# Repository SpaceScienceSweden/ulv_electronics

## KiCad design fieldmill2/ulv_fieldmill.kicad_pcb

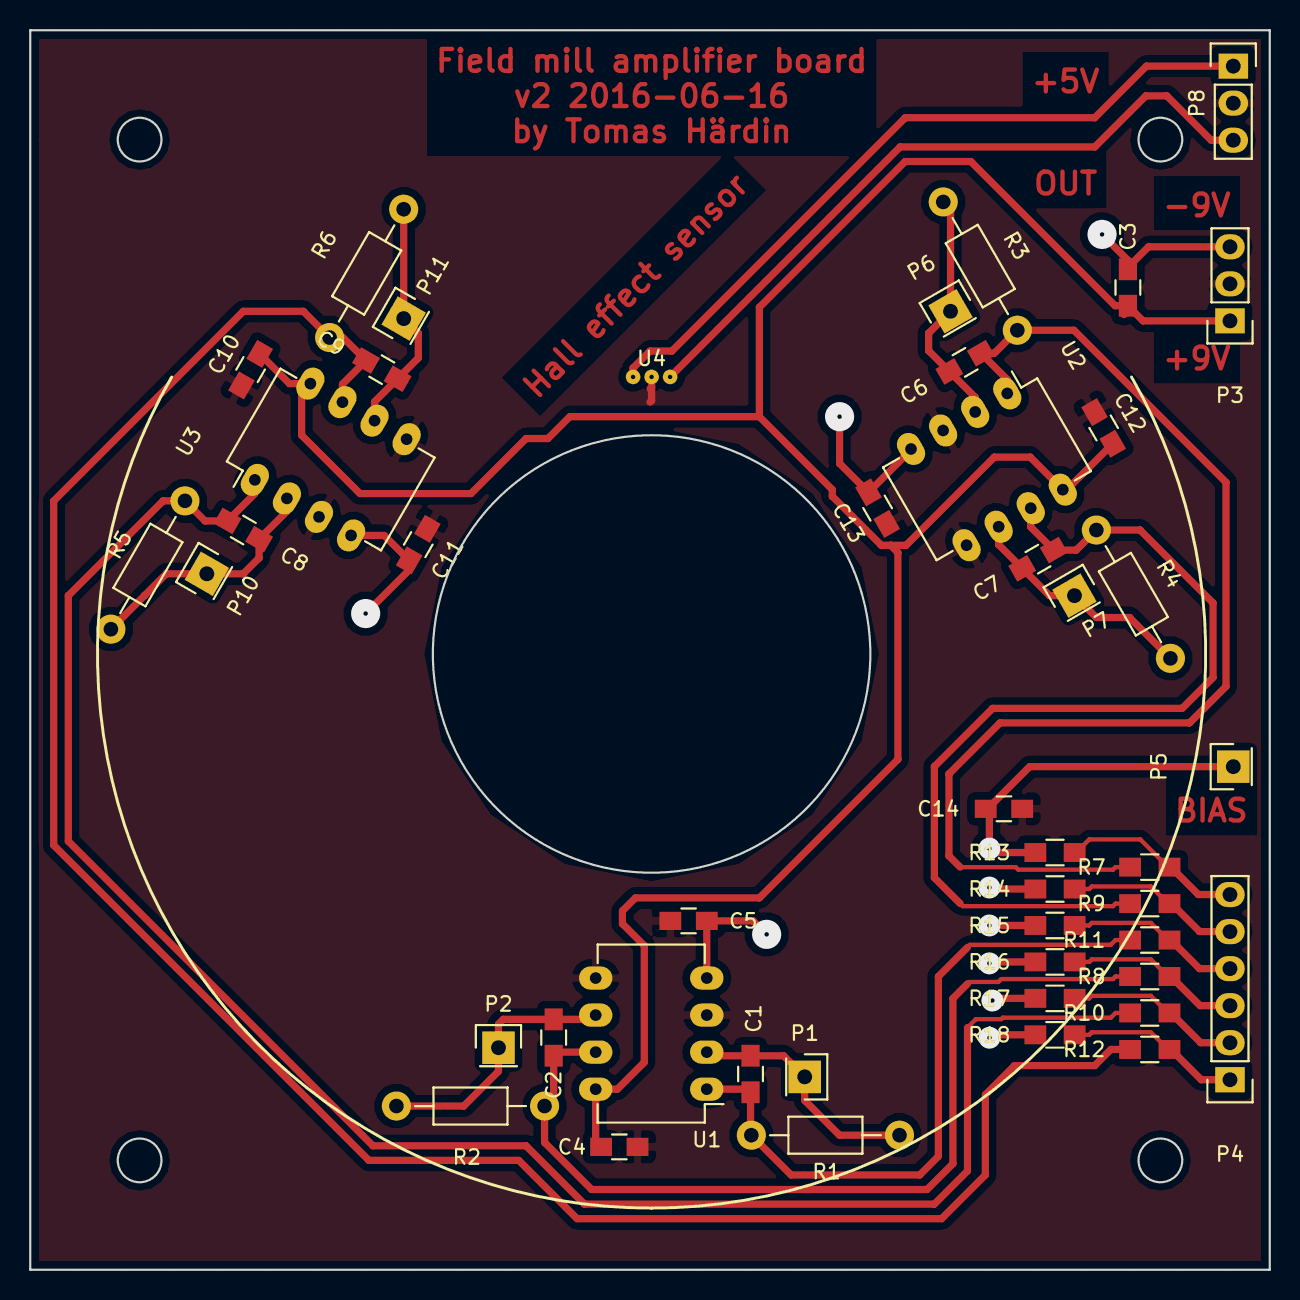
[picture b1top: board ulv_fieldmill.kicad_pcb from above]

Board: 4 copper layers, 85.0 x 85.0 mm, 46 parts (0 on the bottom side), 24 nets.

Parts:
C1, C2, C6, C7, C8, C9: 1p; C_0805_HandSoldering
C3, C14: 1u; C_0805_HandSoldering
C4, C5, C10, C11, C12, C13: 100n; C_0805_HandSoldering
P1, P2, P5, P6, P7, P10, P11: CONN_01X01; Pin_Header_Straight_1x01
P3, P8: CONN_01X03; Pin_Header_Straight_1x03
P4: CONN_01X06; Pin_Header_Straight_1x06
R1, R2, R3, R4, R5, R6: 100M; Resistor_Horizontal_RM10mm
R7, R8, R9, R10, R11, R12, R13, R14, R15, R16, R17, R18: 10k; R_0805_HandSoldering
U1, U2, U3: OPA2604; DIP-8_W7.62mm_LongPads
U4: A3506LU; 3x50mil

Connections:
+5V: P8.1, U4.1
+9VA: C3.2, C4.2, C10.2, C12.2, P3.1, U1.8, U2.8, U3.8
-9VA: C3.1, C5.1, C11.1, C13.1, P3.3, U1.4, U2.4, U3.4
GND: C4.1, C5.2, C10.1, C11.2, C12.1, C13.2, C14.1, P3.2, P8.2, U1.3, U1.5, U2.3, U2.5, U3.3, U3.5, U4.2
unnamed: C1.1, R1.1, R11.2, U1.1
unnamed: C1.2, P1.1, R1.2, U1.2
unnamed: C2.1, R2.1, R8.2, U1.7
unnamed: C2.2, P2.1, R2.2, U1.6
unnamed: C6.1, R3.1, R7.2, U2.1
unnamed: C6.2, P6.1, R3.2, U2.2
unnamed: C7.1, R4.1, R9.2, U2.7
unnamed: C7.2, P7.1, R4.2, U2.6
unnamed: C8.1, R5.1, R10.2, U3.1
unnamed: C8.2, P10.1, R5.2, U3.2
unnamed: C9.1, R6.1, R12.2, U3.7
unnamed: C9.2, P11.1, R6.2, U3.6
unnamed: C14.2, P5.1, R13.2, R14.2, R15.2, R16.2, R17.2, R18.2
unnamed: P4.1, R12.1, R18.1
unnamed: P4.2, R10.1, R17.1
unnamed: P4.3, R8.1, R16.1
unnamed: P4.4, R11.1, R15.1
unnamed: P4.5, R9.1, R14.1
unnamed: P4.6, R7.1, R13.1
unnamed: P8.3, U4.3

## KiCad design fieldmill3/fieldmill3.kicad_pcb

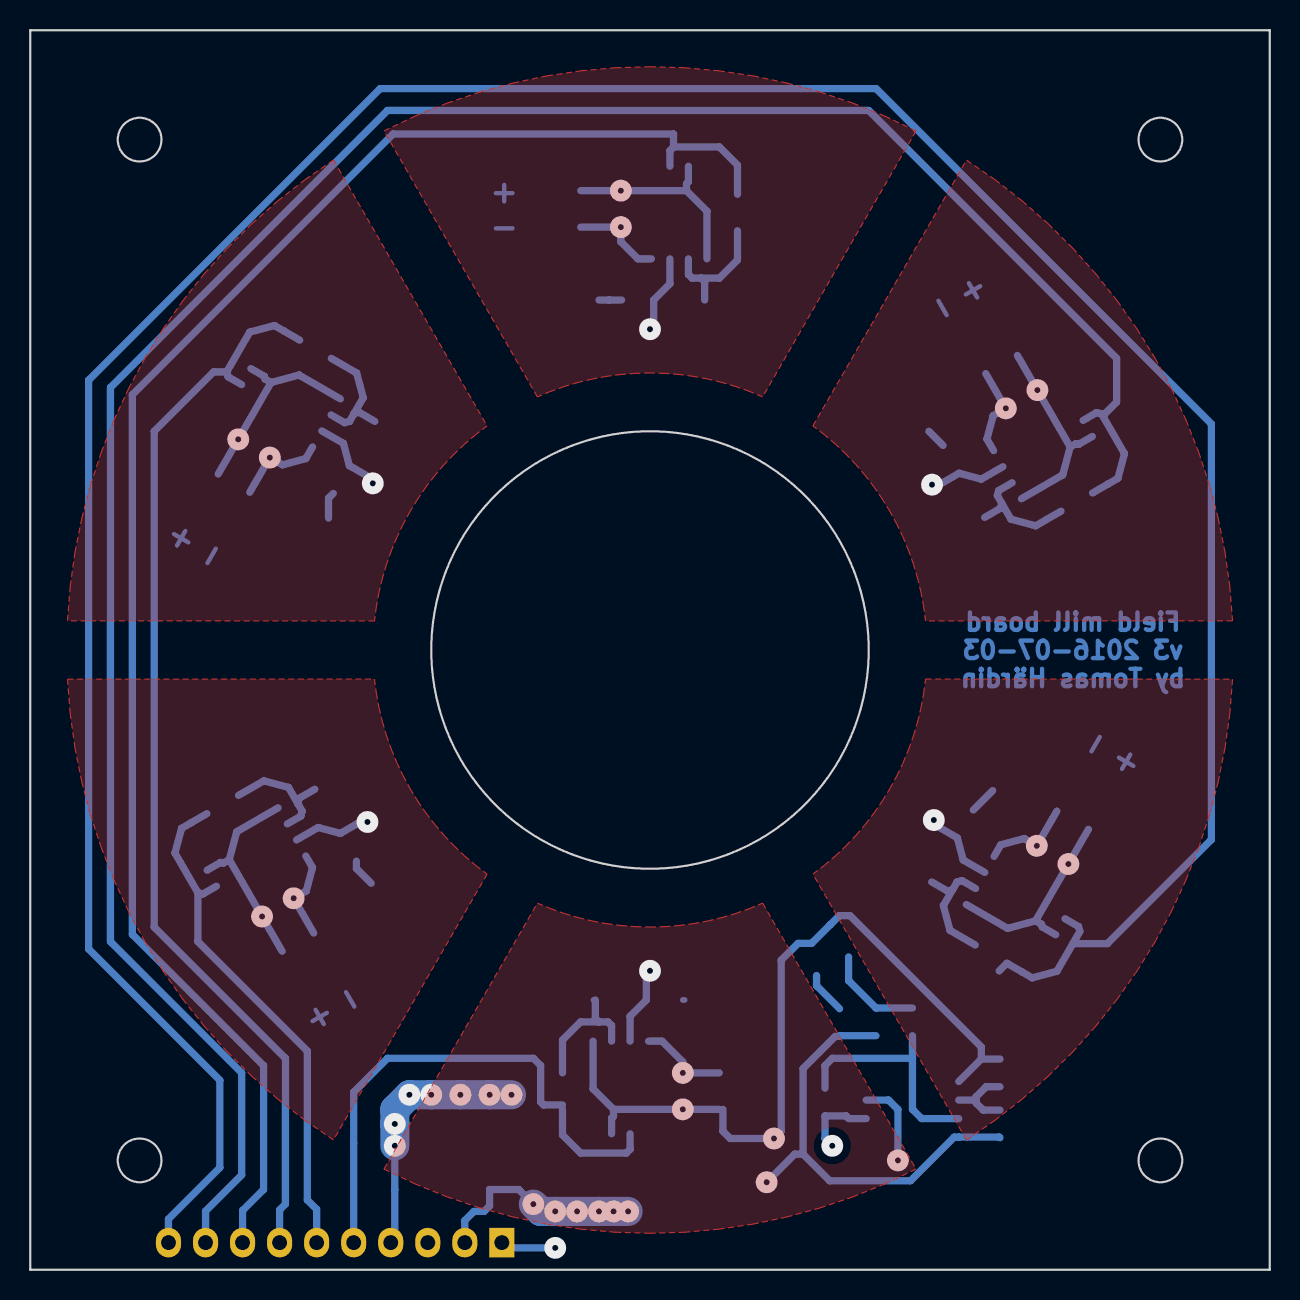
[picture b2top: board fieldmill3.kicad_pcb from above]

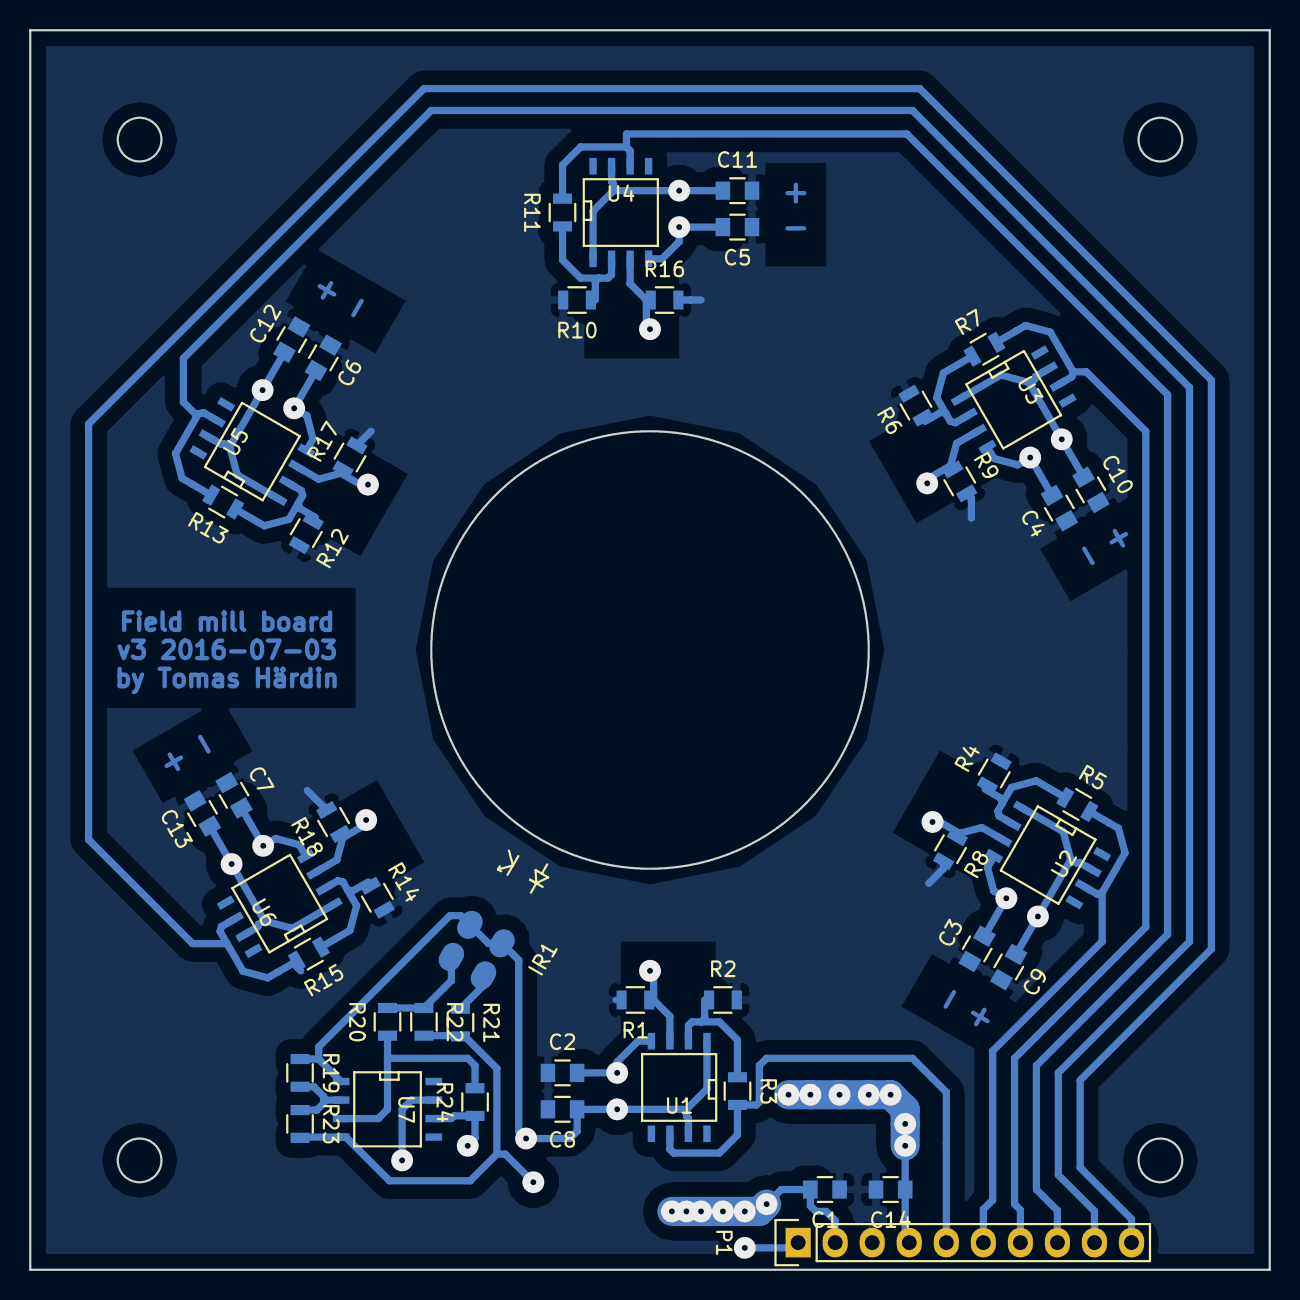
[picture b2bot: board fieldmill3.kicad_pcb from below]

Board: 4 copper layers, 85.0 x 85.0 mm, 47 parts (47 on the bottom side), 26 nets.

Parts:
C1, C14: 10u; C_0805
C2, C3, C4, C5, C6, C7, C8, C9, C10, C11, C12, C13: 100n; C_0805
IR1: ITR20001; ITR20001-smd
P1: CONN_01X10; Pin_Header_Straight_1x10
R1, R8, R9, R16, R17, R18: 10M; R_0805
R2, R4, R6, R10, R12, R14: 10k; R_0805
R3, R5, R7, R11, R13, R15, R19, R20, R22, R23: 100k; R_0805
R21: 2k2; R_0805
R24: 1M; R_0805
U1, U2, U3, U4, U5, U6, U7: MAX4238; SOIC-8-N

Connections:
/GRD1: R2.1, R3.1, U1.2
/GRD2: R4.1, R5.1, U2.2
/GRD3: R6.1, R7.1, U3.2
/GRD4: R10.1, R11.1, U4.2
/GRD5: R12.1, R13.1, U5.2
/GRD6: R14.1, R15.1, U6.2
/SENSOR1: R1.1, U1.3
/SENSOR2: R8.1, U2.3
/SENSOR3: R9.1, U3.3
/SENSOR4: R16.1, U4.3
/SENSOR5: R17.1, U5.3
/SENSOR6: R18.1, U6.3
GND: C1.1, C2.1, C3.1, C4.1, C5.1, C6.1, C7.1, C8.2, C9.2, C10.2, C11.2, C12.2, C13.2, C14.2, P1.3, R1.2, R2.2, R4.2, R6.2, R8.2, R9.2, R10.2, R12.2, R14.2, R16.2, R17.2, R18.2
unnamed: IR1.E, R20.2, R22.1
unnamed: IR1.K, R21.1
unnamed: P1.1, R24.1, U7.6
unnamed: P1.5, R3.2, U1.6
unnamed: P1.6, R5.2, U2.6
unnamed: P1.7, R7.2, U3.6
unnamed: P1.8, R11.2, U4.6
unnamed: P1.9, R13.2, U5.6
unnamed: P1.10, R15.2, U6.6
unnamed: R19.2, R23.1, U7.2
unnamed: R20.1, R24.2, U7.3
VDD: C1.2, C8.1, C9.1, C10.1, C11.1, C12.1, C13.1, IR1.A, IR1.C, P1.2, R19.1, U1.1, U1.7, U2.1, U2.7, U3.1, U3.7, U4.1, U4.7, U5.1, U5.7, U6.1, U6.7, U7.1, U7.7
VSS: C2.2, C3.2, C4.2, C5.2, C6.2, C7.2, C14.1, P1.4, R21.2, R22.2, R23.2, U1.4, U2.4, U3.4, U4.4, U5.4, U6.4, U7.4

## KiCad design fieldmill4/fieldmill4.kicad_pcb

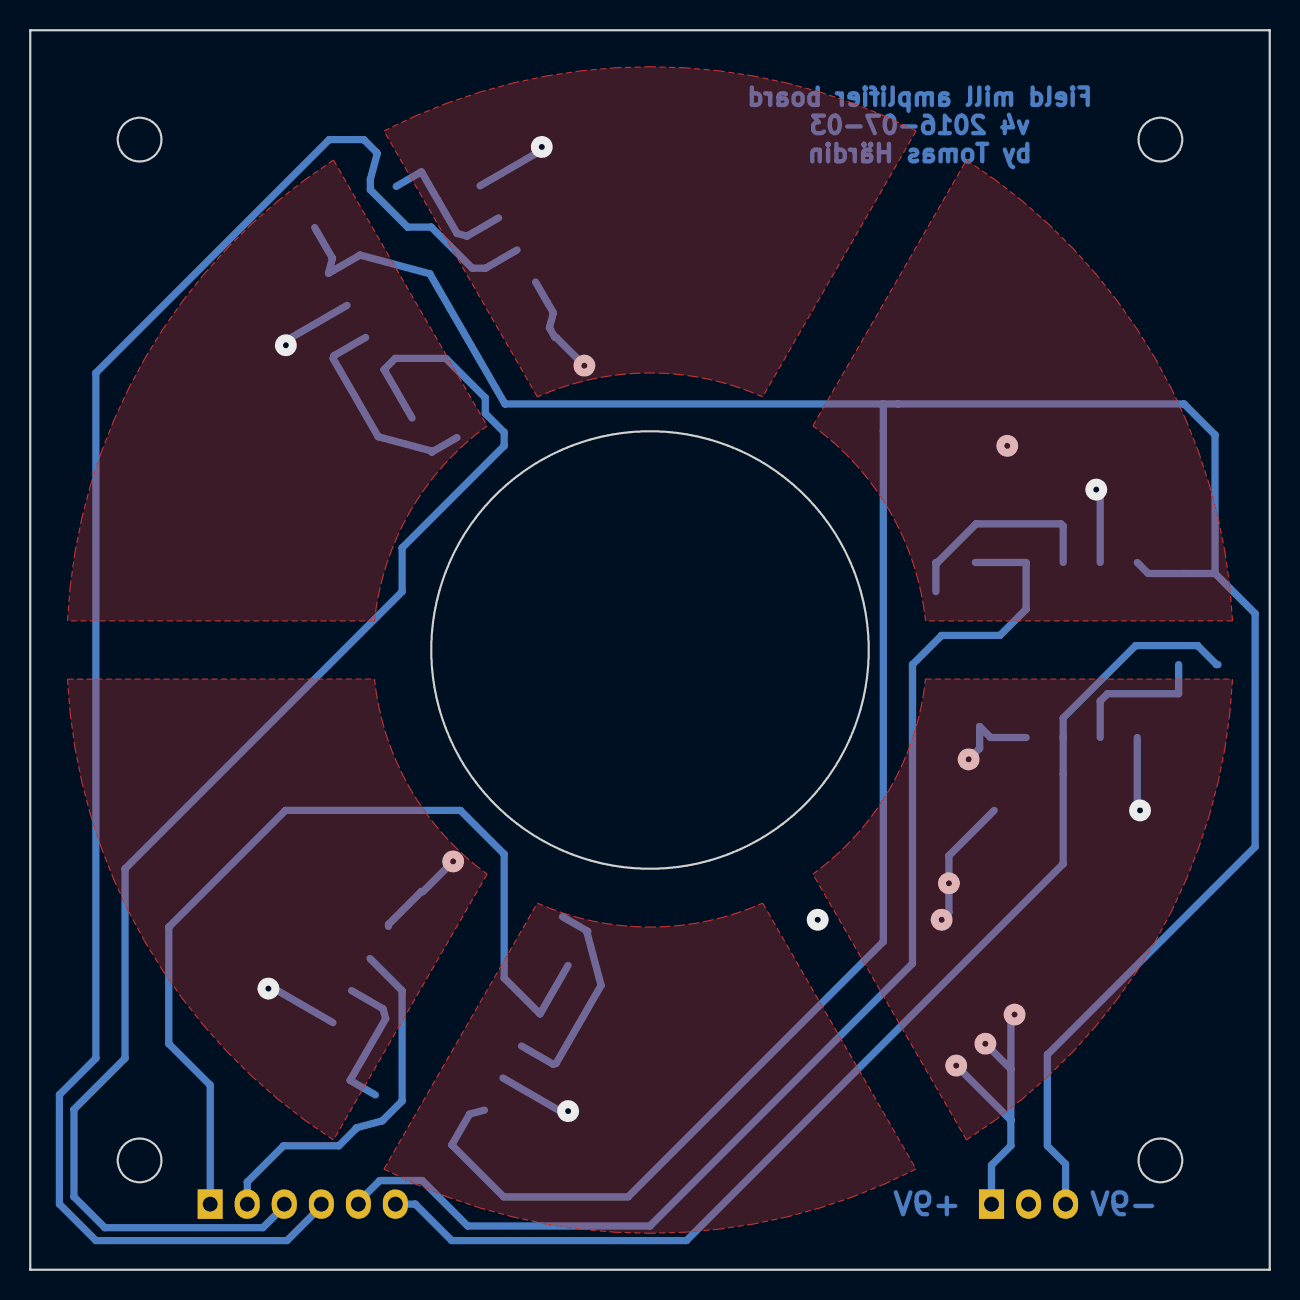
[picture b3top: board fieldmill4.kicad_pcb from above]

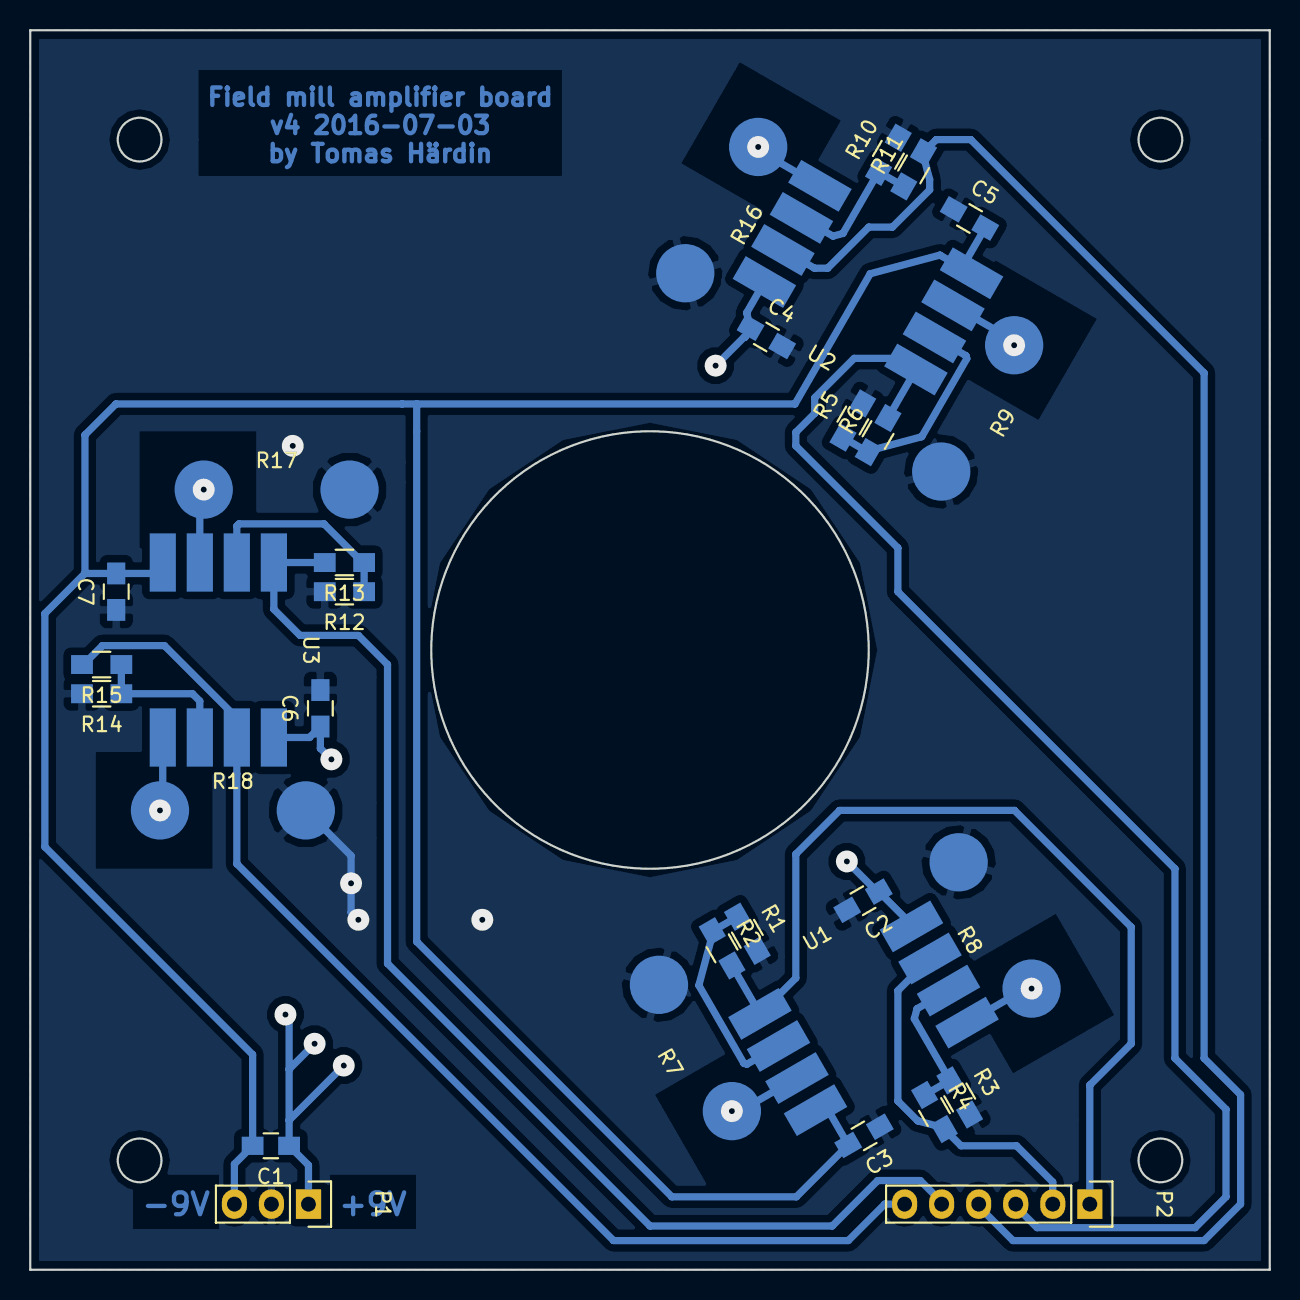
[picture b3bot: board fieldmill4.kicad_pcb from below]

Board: 4 copper layers, 85.0 x 85.0 mm, 30 parts (30 on the bottom side), 21 nets.

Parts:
C1: 10u; C_0805_HandSoldering
C2, C3, C4, C5, C6, C7: 100n; C_0805_HandSoldering
P1: CONN_01X03; Pin_Header_Straight_1x03
P2: CONN_01X06; Pin_Header_Straight_1x06
R1, R3, R5, R10, R12, R14: 10k; R_0805_HandSoldering
R2, R4, R6, R11, R13, R15: 100k; R_0805_HandSoldering
R7, R8, R9, R16, R17, R18: 10M; 10mm-thru-smd
U1, U2, U3: OPA2604; DIP8-SMD

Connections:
+9V: C1.1, C2.1, C4.1, C6.1, P1.1, U1.8, U2.8, U3.8
-9VA: C1.2, C3.2, C5.2, C7.2, P1.3, U1.4, U2.4, U3.4
/GRD1: R1.1, R2.1, U1.2
/GRD2: R3.1, R4.1, U1.6
/GRD3: R5.1, R6.1, U2.2
/GRD4: R10.1, R11.1, U2.6
/GRD5: R12.1, R13.1, U3.2
/GRD6: R14.1, R15.1, U3.6
/SENSOR1: R7.1, U1.3
/SENSOR2: R8.1, U1.5
/SENSOR3: R9.1, U2.3
/SENSOR4: R16.1, U2.5
/SENSOR5: R17.1, U3.3
/SENSOR6: R18.1, U3.5
GND: C2.2, C3.1, C4.2, C5.1, C6.2, C7.1, P1.2, R1.2, R3.2, R5.2, R7.2, R8.2, R9.2, R10.2, R12.2, R14.2, R16.2, R17.2, R18.2
unnamed: P2.1, R2.2, U1.1
unnamed: P2.2, R4.2, U1.7
unnamed: P2.3, R6.2, U2.1
unnamed: P2.4, R11.2, U2.7
unnamed: P2.5, R13.2, U3.1
unnamed: P2.6, R15.2, U3.7

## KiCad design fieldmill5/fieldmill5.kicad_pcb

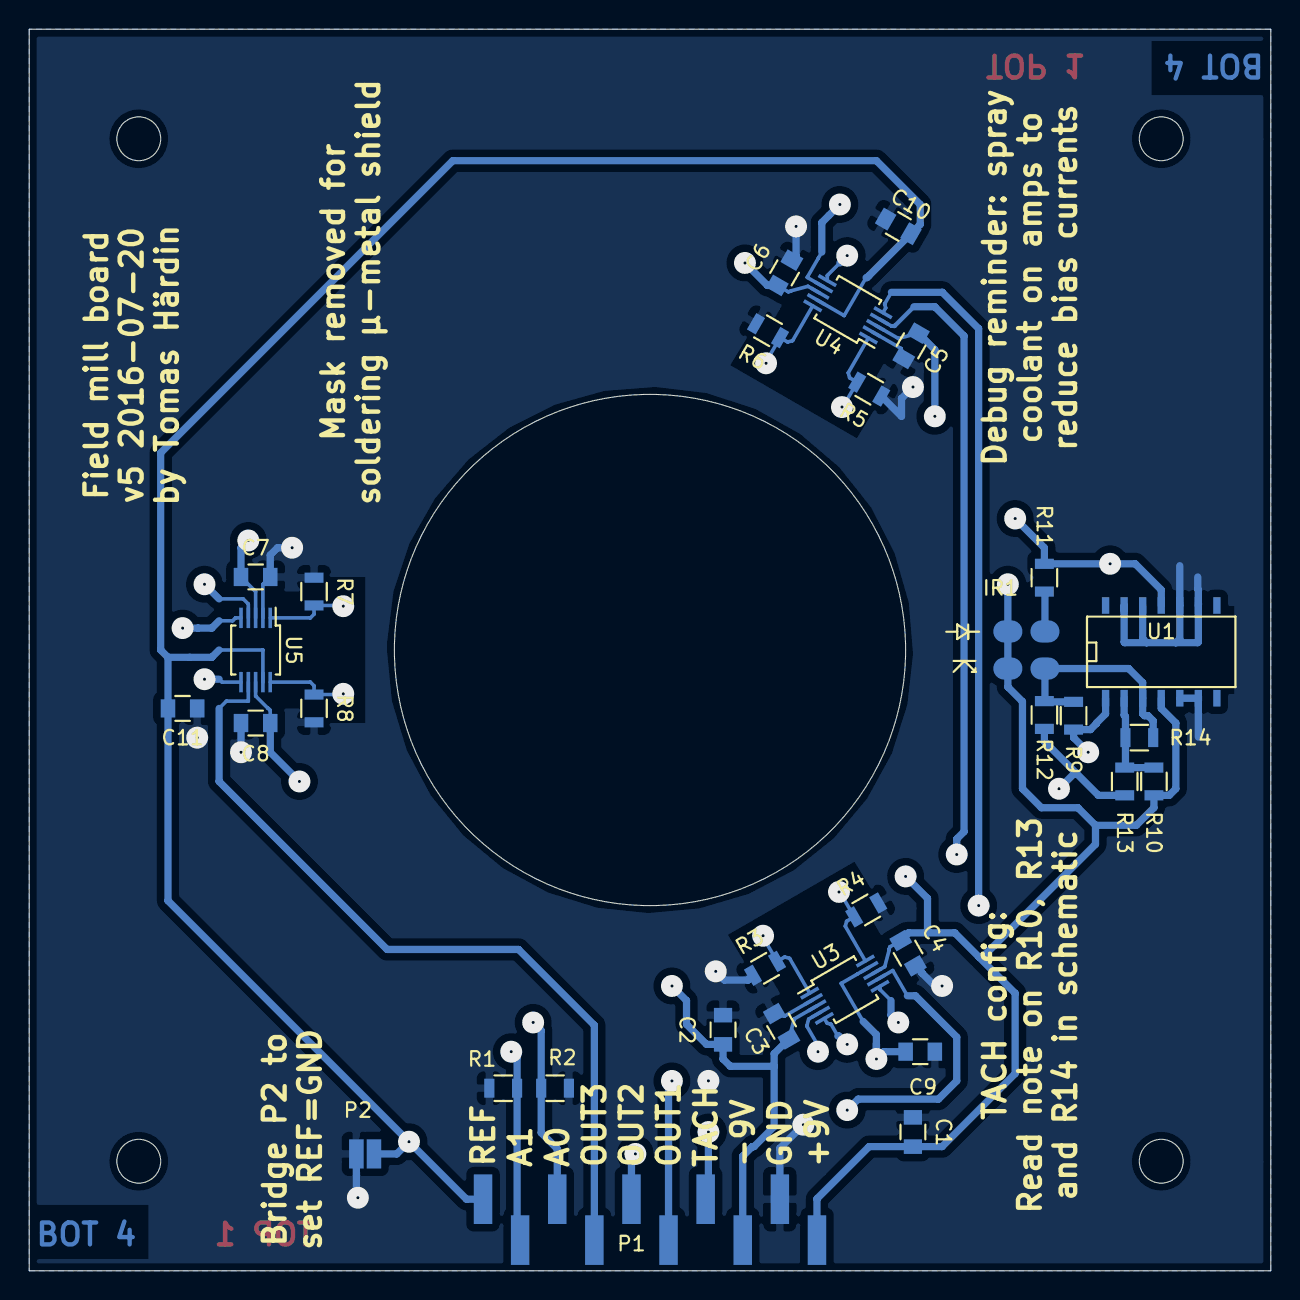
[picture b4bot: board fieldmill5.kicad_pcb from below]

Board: 4 copper layers, 85.0 x 85.0 mm, 32 parts (32 on the bottom side), 19 nets.

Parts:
C1, C2: 10u; C_0805
C3, C4, C5, C6, C7, C8, C9, C10, C11: 100n; C_0805
IR1: ITR20001; ITR20001-smd
P1: CONN_01X10; SMD_pinheader_1x10
P2: CONN_01X02; solder_bridge
R1, R2, R11: 10k; R_0805
R3, R4, R5, R6, R7, R8: 10M; R_0805
R9, R14: 1M; R_0805
R10, R12, R13: 100k; R_0805
U1: LM324; SOIC-14_N
U3, U4, U5: AD8253; MSOP-10_3x3mm_Pitch0.5mm_thinpads

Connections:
+9V: C1.2, C4.1, C6.1, C8.1, IR1.A, IR1.C, P1.1, R10.1, U1.4, U3.8, U4.8, U5.8
-9VA: C2.2, C3.2, C5.2, C7.2, P1.3, R11.2, R12.2, R13.2, U1.11, U3.3, U3.6, U4.3, U4.6, U5.3, U5.6
/TACH: P1.4, R9.2, U1.1
/channel1/A0: P1.8, R2.1, U3.4, U4.4, U5.4
/channel1/A1: P1.9, R1.1, U3.5, U4.5, U5.5
/channel1/OUT: P1.5, U3.7
/channel1/REF: C9.1, C10.1, C11.1, P1.10, P2.2, U3.9, U4.9, U5.9
/channel1/SENSORN: R3.2, U3.1
/channel1/SENSORP: R4.1, U3.10
/channel2/OUT: P1.6, U4.7
/channel2/SENSORN: R5.2, U4.1
/channel2/SENSORP: R6.1, U4.10
/channel3/OUT: P1.7, U5.7
/channel3/SENSORN: R7.2, U5.1
/channel3/SENSORP: R8.1, U5.10
GND: C1.1, C2.1, C3.1, C4.2, C5.1, C6.2, C7.1, C8.2, C9.2, C10.2, C11.2, P1.2, P2.1, R1.2, R2.2, R3.1, R4.2, R5.1, R6.2, R7.1, R8.2, U1.5, U1.6, U1.9, U1.10, U1.12, U1.13, U3.2, U4.2, U5.2
unnamed: IR1.E, R9.1, R12.1, R14.1, U1.3
unnamed: IR1.K, R11.1
unnamed: R10.2, R13.1, R14.2, U1.2

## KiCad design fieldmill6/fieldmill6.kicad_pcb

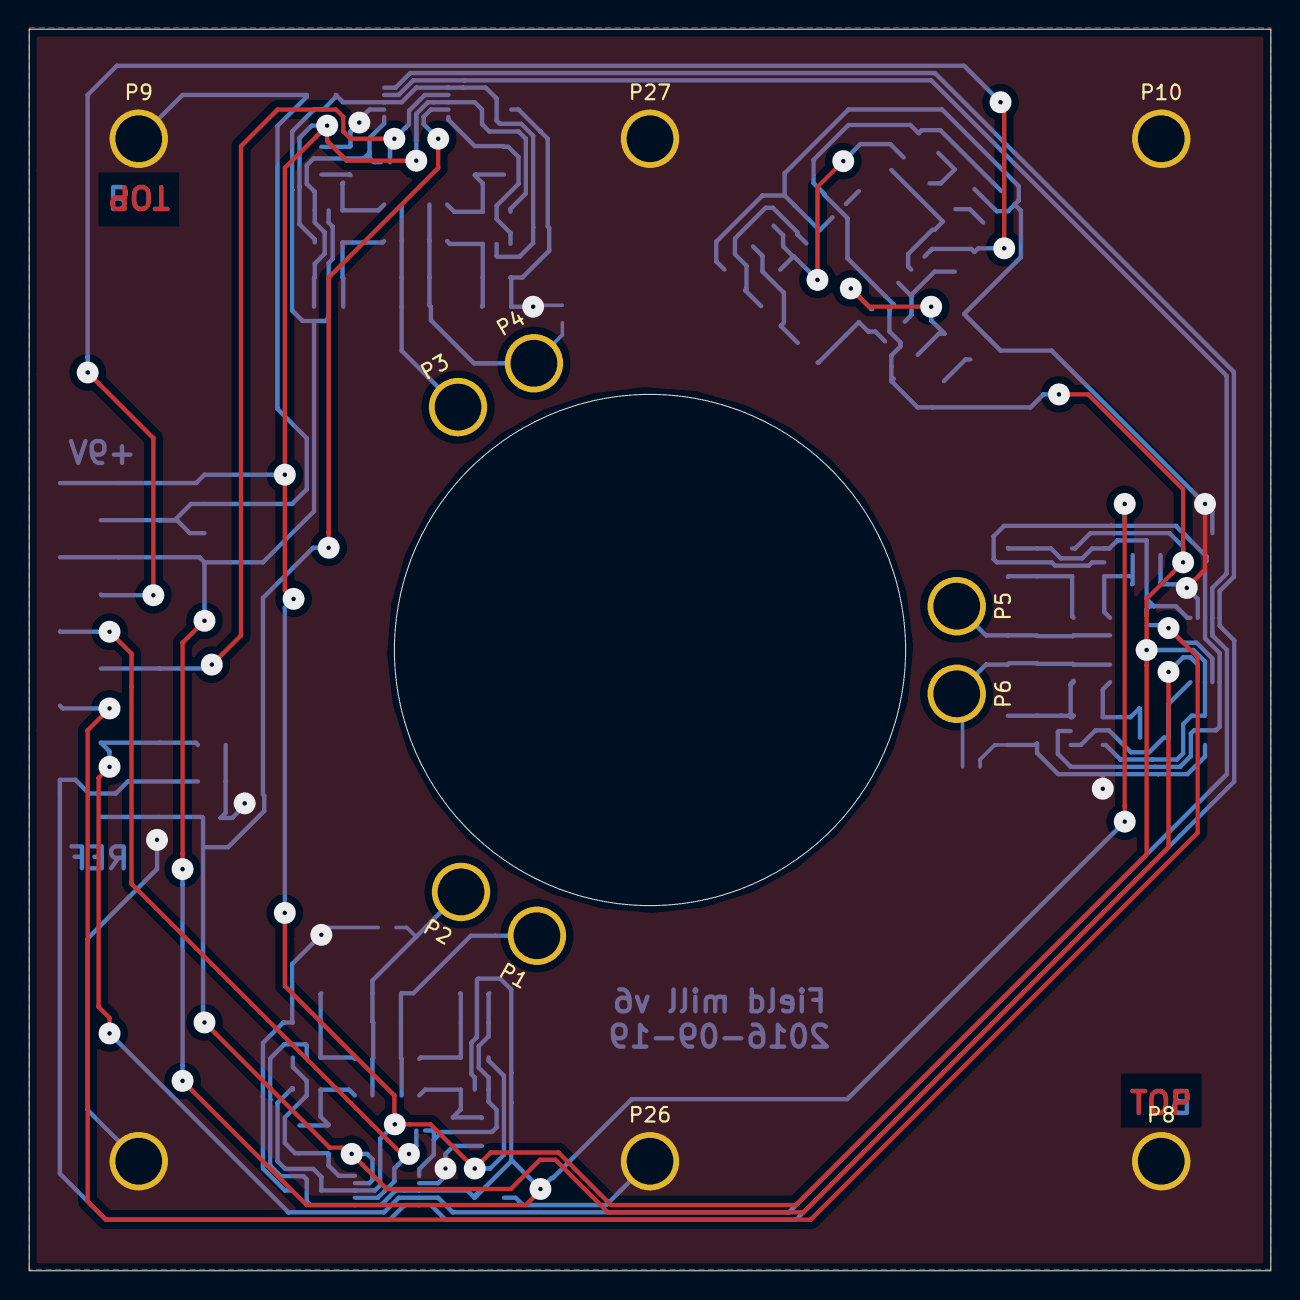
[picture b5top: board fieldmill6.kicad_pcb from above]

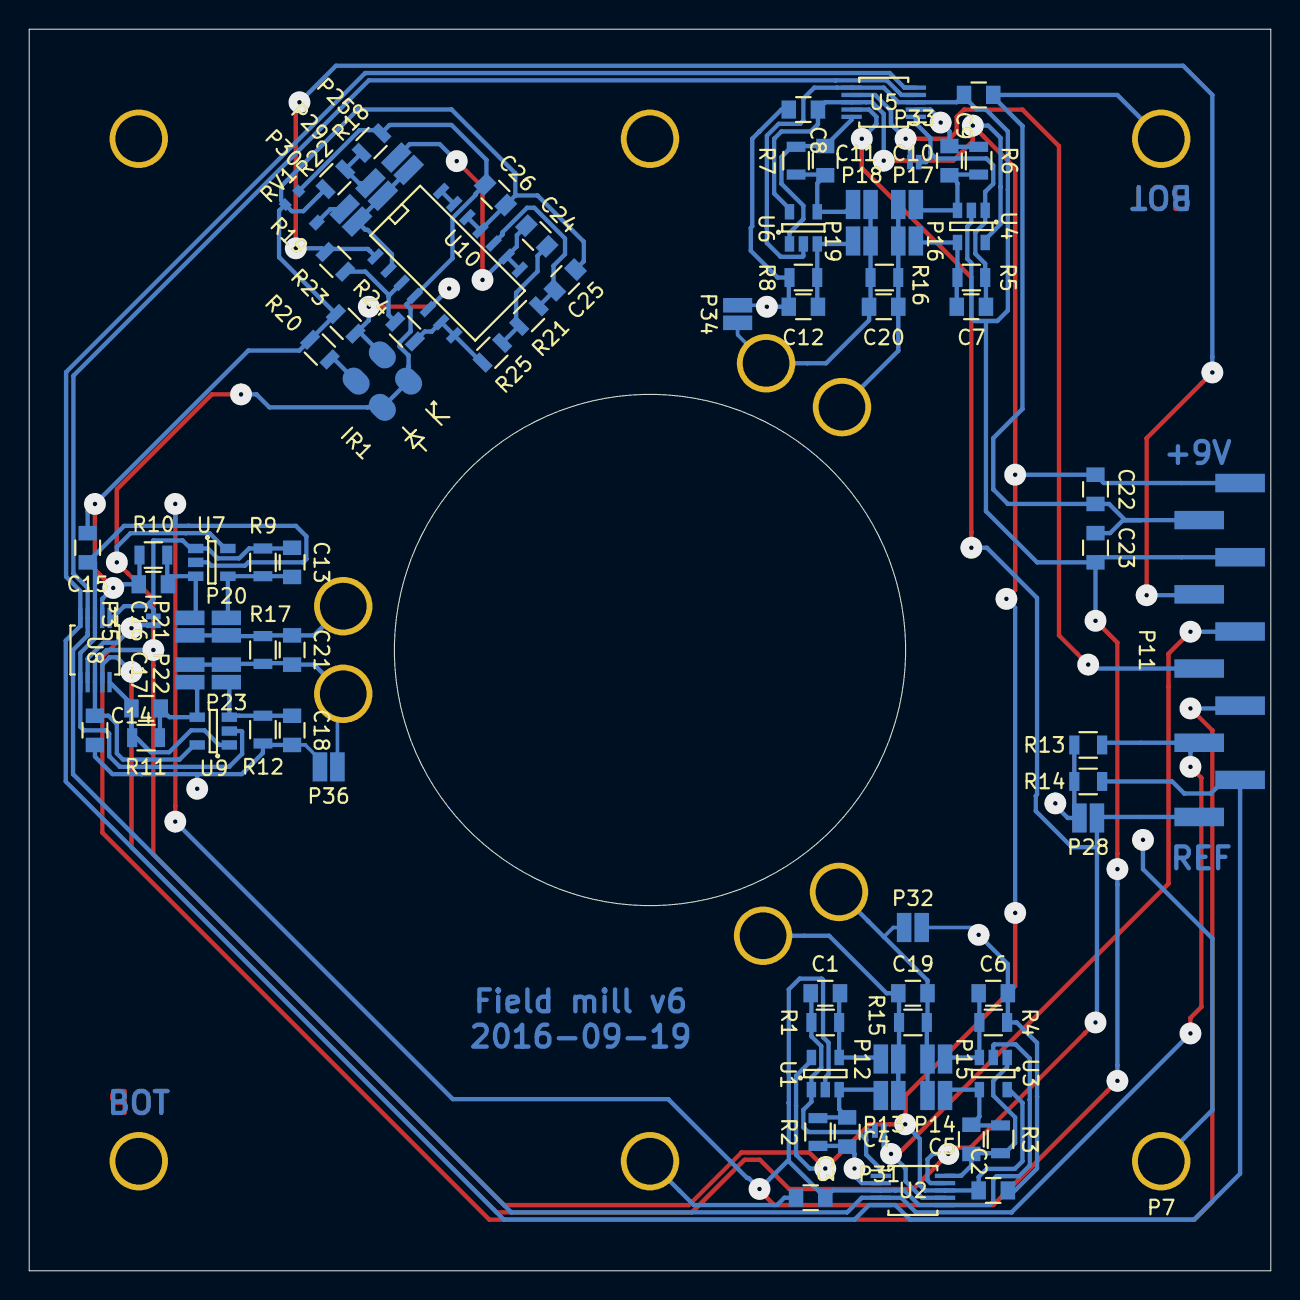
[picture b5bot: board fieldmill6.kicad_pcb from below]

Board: 2 copper layers, 85.0 x 85.0 mm, 98 parts (87 on the bottom side), 45 nets.

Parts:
C1, C5, C7, C11, C13, C17: 150p; C_0805
C2, C3, C8, C9, C14, C15, C26: 100n; C_0805
C4, C6, C10, C12, C16, C18: 15p; C_0805
C19, C20, C21: 0p; C_0805
C22, C23: 10u; C_0805
C24, C25: 1u; C_0805
IR1: ITR20001; ITR20001-smd
P1, P2, P3, P4, P5, P6: SENSOR; M3_PTH
P7, P8, P9, P10, P26, P27: M3; M3_PTH
P11: CONN_01X10; SMD_pinheader_1x10
P12, P14, P16, P18, P20, P22: TRANSIMP; solder_bridge
P13, P15, P17, P19, P21, P23: BUFFER; solder_bridge
P25: RC; solder_bridge
P28: ZEROREF; solder_bridge
P29: FIXED; solder_bridge
P30: POT; solder_bridge
P31, P33, P35: NODIFF; solder_bridge_1mm
P32, P34, P36: GND_N; solder_bridge
R1, R2, R3, R4, R5, R6, R7, R8, R9, R10, R11, R12, R19: 1M; R_0805
R13, R14: 10k; R_0805
R15, R16, R17: 1T; R_0805
R18: 220k; R_0805
R20: 5k6; R_0805
R21, R22, R23, R24, R25: 100k; R_0805
RV1: 100k; PVZ2A
U1, U3, U4, U6, U7, U9: LM6211MF; SOT-23-5
U2, U5, U8: AD8253; MSOP-10_3x3mm_Pitch0.5mm
U10: LM324; SOIC-14_N

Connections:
+9V: C2.1, C8.1, C14.1, C22.1, C26.1, IR1.A, IR1.C, P11.1, R18.1, RV1.1, U1.5, U2.8, U3.5, U4.5, U5.8, U6.5, U7.5, U8.8, U9.5, U10.4
-9VA: C3.2, C9.2, C15.2, C23.2, P11.3, U1.2, U2.3, U2.6, U3.2, U4.2, U5.3, U5.6, U6.2, U7.2, U8.3, U8.6, U9.2
/TACH: P11.4, R19.2, U10.1
/channel1/OUT: P11.5, P31.2, U2.7
/channel1/SENSORN: C19.2, P2.1, P14.2, P15.1, P32.1, R15.1
/channel1/SENSORP: C19.1, P1.1, P12.2, P13.1, R15.2
/channel2/OUT: P11.6, P33.2, U5.7
/channel2/SENSORN: C20.2, P4.1, P18.2, P19.1, P34.1, R16.1
/channel2/SENSORP: C20.1, P3.1, P16.2, P17.1, R16.2
/channel3/OUT: P11.7, P35.2, U8.7
/channel3/SENSORN: C21.2, P6.1, P22.2, P23.1, P36.1, R17.1
/channel3/SENSORP: C21.1, P5.1, P20.2, P21.1, R17.2
A0: P11.8, R13.1, U2.4, U5.4, U8.4
A1: P11.9, R14.1, U2.5, U5.5, U8.5
GND: C2.2, C3.1, C4.2, C6.2, C8.2, C9.1, C10.2, C12.2, C14.2, C15.1, C16.2, C18.2, C22.2, C23.1, C25.2, C26.2, P7.1, P8.1, P9.1, P10.1, P11.2, P26.1, P27.1, P28.1, P32.2, P34.2, P36.2, R2.1, R4.1, R6.1, R8.1, R10.1, R12.1, R13.2, R14.2, R20.2, R22.2, R23.2, RV1.3, U2.2, U5.2, U8.2, U10.11, U10.12
unnamed: C1.1, P31.1, R1.1, U1.1, U2.1
unnamed: C1.2, P12.1, R1.2, U1.4
unnamed: C4.1, P13.2, R2.2, U1.3
unnamed: C5.1, R3.1, U2.10, U3.1
unnamed: C5.2, P14.1, R3.2, U3.4
unnamed: C6.1, P15.2, R4.2, U3.3
unnamed: C7.1, P33.1, R5.1, U4.1, U5.1
unnamed: C7.2, P16.1, R5.2, U4.4
unnamed: C10.1, P17.2, R6.2, U4.3
unnamed: C11.1, R7.1, U5.10, U6.1
unnamed: C11.2, P18.1, R7.2, U6.4
unnamed: C12.1, P19.2, R8.2, U6.3
unnamed: C13.1, P35.1, R9.1, U7.1, U8.1
unnamed: C13.2, P20.1, R9.2, U7.4
unnamed: C16.1, P21.2, R10.2, U7.3
unnamed: C17.1, R11.1, U8.10, U9.1
unnamed: C17.2, P22.1, R11.2, U9.4
unnamed: C18.1, P23.2, R12.2, U9.3
unnamed: C24.1, P25.2, U10.8, U10.9
unnamed: C24.2, R21.2, R25.1
unnamed: C25.1, R21.1, U10.10
unnamed: IR1.E, R23.1, U10.5
unnamed: IR1.K, R20.1
unnamed: P25.1, P29.1, P30.1, U10.2
unnamed: P29.2, R18.2, R22.1
unnamed: P30.2, RV1.2
unnamed: R19.1, R24.2, U10.3
unnamed: R24.1, R25.2, U10.6, U10.7
unnamed: U10.13, U10.14
REF: P11.10, P28.2, U2.9, U5.9, U8.9
